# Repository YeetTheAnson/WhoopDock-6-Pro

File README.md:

# WhoopDock 6 Pro

## Introduction

*Up to 130W when powered with VBUS pads

This is my custom BT2.0 battery charger! I started this project because I wanted a programmable 1S LiPo/LiHV multi channel charger that included discharging and storage mode. Commercial chargers like the hexachargers or whoopstor has all the mentioned features but it's limited and lack customizability.

This charger is designed primarily for tinywhoop FPV drone batteries that uses the BetaFPV BT2.0 connector, but its 5A charge current also allows it to be used with larger cylindrical cell batteries for long range drones.

| Feature | WhoopDock 6 Pro | BetaFPV Hexacharger | ViFly WhoopStor V3 |
| --- | --- | --- | --- |
| **Max Charge Current (Per Channel)** | **Up to 5A**  | 3.0A | 1.3A |
| **Max Discharge Current (Per Channel)** | **1.16A** | 0.4A | 0.3A |
| **Custom Discharge Current** | **Yes**  | No | No |
| **Target Voltage Control** | **Fully Customizable** | Presets Only | Presets Only |
| **Voltage Increments** | **16mV** | None (3.85V/4.2V/4.35V) | None (3.8V/3.85V/4.2V/4.35V) |
| **Current Increments** | **64mA** | 500mA | 100mA |
| **Big Colour Screen** | **Yes** | **Yes** | No |
| **Programmability** | **Yes** (Arduino compatible) | No (Closed source) | No (Closed source) |
| **WiFi & Bluetooth** | **Yes** | No | No |
| **Audio Feedback** | **Yes** | **Yes** | **Yes** |
| **Active Cooling** | **Yes** (Programmable fan curve) | **Yes** | **Yes** |
| **Reverse Polarity Protection** | **Yes** | No | **Yes** |

If you don't like how it works, you could always program it to replicate the behavior of your favorite charger.

### Advantages:

* **Current Delivery:** The WhoopDock is much more powerful compared to commercial chargers from BetaFPV and ViFly. With the BQ25890, you can charge large batteries up to 5A, or use the small 64mA interval to precisely control the charge current of small batteries. The 1.16A discharge rate means your large batteries will hit storage voltage way faster, and can be adjusted lower for smaller batteries.
* **Fine Control:** Instead of being forced to choose from specific presets, the 16mV step resolution allows you to charge different battery chemistries or set a custom charge termination voltage.
* **Connectivity:** Having Bluetooth and WiFi onboard allows you to monitor charge cycles from your phone, and receive push notifications when charging is complete.

### Drawbacks:
* **Max power:** While the WhoopDock 60W power is still more than the hexacharger's 24W, the pro version supports up to 78W. The 60W limit is due to the USB C specification, and it supports up to 130W if powered directly by bypassing USB connectors.
* **No PH2.0 connector:** This is intentional by design as PH2.0 is an inferior connector compared to BT2.0, and it only supports a continuous charge current of 2A.

---

## Hardware Specifications

* **MCU:** ESP32-S3-WROOM-1-N8
* **Charge Controller:** 6x TI BQ25890
* **I2C Multiplexer:** TCA9548A
* **PD Negotiation:** CH224K
* **Display:** 1.3" 240x240 ST7789 TFT
* **Power Supply:** XL1509-5.0E1 5V Buck Converter, 2x RT9193 3.3v LDO (One for ESP32 and another to power the display)
* **Active Cooling:** 5V 4010 blower fan and dual 60x20x10mm aluminum heatsinks
* **Protection:** AO4407A P Channel MOSFETs for battery reverse polarity insertion protection

Note: The BQ25890 has a maximum input voltage limit of 14V. The CH224K is configured to negotiate 12V for optimal performance. Do not bridge the 15V or 20V jumpers on the PD controller. Only use 2-3s batteries on the VBUS input pads.

---

> [!WARNING]
> **DO NOT USE THE OCTAL PSRAM VERSION OF THE ESP32S3.** The octal version uses GPIO35, 36 and 37 for memory which overlap with the GPIOs used in the charger. Use QUAD SPI versions otherwise the ESP32 will fail to boot.

## Ports and Interfaces

### External Connections

* **Main Power (Protruding USB C):** This is the primary power input and supports up to 12v 5A (60W)
* **Programming (Flush USB C):** Connected directly to the ESP32 USB data pins for programming. Cannot be accessed while inside the case.
* **Direct Power Pads:** Exposed solder pads on the PCB to bypass the USBC port entirely. Solder XT30 connectors here to bypass the power limit of USB C

### Pinout

| Component | Pin Name | ESP32S3 GPIO | Description |
| --- | --- | --- | --- |
| **TFT Display** | `SCL`| GPIO 35 | SPI Clock |
|  | `TFT_SDA`| GPIO 36 | SPI Data |
|  | `TFT_RES` | GPIO 37 | Display Reset |
|  | `TFT_DC` | GPIO 38 | Data / Command |
|  | `TFT_BLK` | GPIO 39 | Backlight Control |
| **I2C Bus** | `MAIN_SDA` | GPIO 47 | Main I2C Data (TCA9548A MUX) |
|  | `MAIN_SCL` | GPIO 48 | Main I2C Clock (TCA9548A MUX) |
| **User Interface** | `SW_LEFT` | GPIO 8 | Left Button (Active Low) |
|  | `SW_RIGHT` | GPIO 18 | Right Button (Active Low) |
|  | `BUZZER` | GPIO 17 | Passive Buzzer |
| **Cooling** | `FAN` | GPIO 40 | 4010 Fan PWM Power |

*Note: The CE pins are pulled high by 5.1k resistors.*

|Battery Channel | Charge Enable GPIO | Discharge PWM GPIO | TCA9548A MUX Port |
| --- | --- | --- | --- |
| **Channel 1** | GPIO 43 | GPIO 41 | Port 6 |
| **Channel 2** | GPIO 2 | GPIO 42 | Port 5 |
| **Channel 3** | GPIO 1 | GPIO 44 | Port 4 |
| **Channel 4** | GPIO 12 | GPIO 13 | Port 1 |
| **Channel 5** | GPIO 11 | GPIO 14 | Port 2 |
| **Channel 6** | GPIO 10 | GPIO 21 | Port 3 |

---

## Firmware Setup

The current firmware is for connection validation only, and isn't production ready yet. Your batteries WILL charge
### How to flash the firmware

1. **Connect to the Programming Port:** Plug a USBC cable into the flush USBC port (not the protruding power port).
2. **Open Arduino IDE:** Load `firmware/firmware.ino`.
3. **Select Board:** Choose "ESP32S3 Dev Module". Ensure "USB CDC On Boot" is enabled to view the serial monitor for debugging.
4. **Flash:** Click upload. The firmware will initialize the ST7789 display, ramp up and down the fan and buzzer, scans the I2C multiplexer ports and then reports the status of all BQ25890 to the serial monitor.

---

## Case Assembly

### 3D Printed Parts

All STL files for the case is in `/production/3dPrint/`.

* `bottomCase.stl`
* `topCase.stl`
* `Buttons.stl`
* `Feets.stl`

### Assembly

1. Create a solder bridge at CFG3 to set the Ch224K to 12V

2. Trim the BetaFPV BT2.0 connector legs. Make a test fit **before** soldering to ensure it's not protruding.

3. Place the 3D printed `Buttons.stl` into the holes on `topCase.stl`.

4. Screw in the 4010 blower fan into the bottom case using 4x M2x6mm screws.

5. Snap the PCB into the top case.

6. Apply thermal adhesives on the two heatsink and attach to the PCB.

7. Secure the bottom case onto the top case and screw in using 4x M2x6mm screws. Remember to solder the solder the fan wires before closing the case.

8. Attach the TPU  `Feets.stl` to the bottom to cover the screws and prevent sliding. You may use glue to keep the feets in.

---

## Bill of Material

Note: The prices in USD are converted as of 13 August 2026 and prices may fluctuate. Promo codes will be applied before checkout to bring the costs down. And yes, the costs of separate components are cheaper than JLCPCB assembly.

| Item Name | Link | Vendor | Quantity | Total Price (USD) |
| --- | --- | --- | --- | ---: |
| Heatsink 60x20x10mm | [Link](https://shopee.com.my/Heatsink-40x40x11-mm-Aluminium-Clear-Black-Gold-Anodized-i.6674515.812567757) | Shopee | 2 | 0.85 |
| MLT8530 Buzzer 5v | [Link](https://shopee.com.my/5Pcs-SMD-Magnetic-Piezo-Loudspeaker-Speaker-Buzzer-8630-1109-9045-9025-9018-5020-1230-9032-7525-8630-8540-Passive-9650-Active-i.1649836180.27542857025) | Shopee | 1 | 1.45 |
| Capacitor 100nF 50v (0603) | [Link](https://shopee.com.my/100pcs-0603-1608-SMD-Chip-Multilayer-Ceramic-Capacitor-0.1pF-22uF-10pF-22pF-100pF-1nF-10nF-15nF-100nF-0.1uF-1uF-2.2uF-4.7uF-10-i.1649836180.27542857041) | Shopee | 1 | 0.90 |
| Capacitor 10nF 50v (0603) | [Link](https://shopee.com.my/100pcs-0603-1608-SMD-Chip-Multilayer-Ceramic-Capacitor-0.1pF-22uF-10pF-22pF-100pF-1nF-10nF-15nF-100nF-0.1uF-1uF-2.2uF-4.7uF-10-i.1649836180.27542857041) | Shopee | 1 | 0.98 |
| Capacitor 1uF 25v (0603) | [Link](https://shopee.com.my/100pcs-0603-1608-SMD-Chip-Multilayer-Ceramic-Capacitor-0.1pF-22uF-10pF-22pF-100pF-1nF-10nF-15nF-100nF-0.1uF-1uF-2.2uF-4.7uF-10-i.1649836180.27542857041) | Shopee | 1 | 0.91 |
| Capacitor 47nF 50v (0603) | [Link](https://shopee.com.my/100pcs-0603-1608-SMD-Chip-Multilayer-Ceramic-Capacitor-0.1pF-22uF-10pF-22pF-100pF-1nF-10nF-15nF-100nF-0.1uF-1uF-2.2uF-4.7uF-10-i.1649836180.27542857041) | Shopee | 1 | 0.94 |
| Capacitor 4.7uF 16v (0603) | [Link](https://shopee.com.my/100pcs-0603-1608-SMD-Chip-Multilayer-Ceramic-Capacitor-0.1pF-22uF-10pF-22pF-100pF-1nF-10nF-15nF-100nF-0.1uF-1uF-2.2uF-4.7uF-10-i.1649836180.27542857041) | Shopee | 1 | 1.50 |
| Capacitor 10uF 25v (0805) | [Link](https://shopee.com.my/100pcs-0805-SMD-Chip-Multilayer-Ceramic-Capacitor-0.5pF-47uF-10pF-22pF-100pF-1nF-10nF-100nF-0.1uF-1uF-2.2uF-4.7uF-10uF-22uF-i.1649836180.56864018438) | Shopee | 1 | 3.86 |
| Tantalum Capacitor 33uF 10v (A) | [Link](https://shopee.com.my/10Pcs-3216A-SMD-Tantalum-Capacitor-100-220-330-470-1UF-2.2UF-3.3UF-4.7UF-6.8UF-22UF-33UF-47UF-100UF-4V-6.3V-10V-16V-20V-25V-35V-i.1649836180.55607396414) | Shopee | 1 | 1.90 |
| Diode SS14 | [Link](https://shopee.com.my/10-Pieces-SB1045L-SB10100L-SL1045-B240A-SS12-SS14-SS16-SS24-SS26-SS34-SS36-SS54-SS56-SS110-SS210-SS2200-DSK16-DSK24-DSK26-i.1649836180.47204908404) | Shopee | 1 | 0.82 |
| Inductor 1uH (0420) | [Link](https://shopee.com.my/5PCS-SMD-Molding-Power-Inductors-0420-0520-0530-0630-0650-1040-1265-1R0-2R2-6R8-1UH-2.2-3.3-4.7-6.8-33-100UH-2.2UH-Inductance-i.1649836180.45952518693) | Shopee | 2 | 2.10 |
| Resistor 5.1k (0603) | [Link](https://shopee.com.my/200pcs-0603-5-SMD-Resistor-0R-~-10M-1-10W-10-100-150-220-330-470-ohm-1K-2.2K-4.7K-10K-100K-1M-1R-10R-100R-150R-220R-330R-470R-i.1649836180.57850021816) | Shopee | 1 | 0.75 |
| Resistor 10k (0603) | [Link](https://shopee.com.my/200pcs-0603-5-SMD-Resistor-0R-~-10M-1-10W-10-100-150-220-330-470-ohm-1K-2.2K-4.7K-10K-100K-1M-1R-10R-100R-150R-220R-330R-470R-i.1649836180.57850021816) | Shopee | 1 | 0.75 |
| Resistor 1k (0603) | [Link](https://shopee.com.my/200pcs-0603-5-SMD-Resistor-0R-~-10M-1-10W-10-100-150-220-330-470-ohm-1K-2.2K-4.7K-10K-100K-1M-1R-10R-100R-150R-220R-330R-470R-i.1649836180.57850021816) | Shopee | 1 | 0.75 |
| Resistor 100 (0603) | [Link](https://shopee.com.my/200pcs-0603-5-SMD-Resistor-0R-~-10M-1-10W-10-100-150-220-330-470-ohm-1K-2.2K-4.7K-10K-100K-1M-1R-10R-100R-150R-220R-330R-470R-i.1649836180.57850021816) | Shopee | 1 | 0.75 |
| ESP32-S3-WROOM-1-N8 | [Link](https://shopee.com.my/1Pcs-ESP32-S3-ESP32-S3-WROOM-1-1U-ESP32-S3-MINI-1U-4MB-8MB-16MB-N4-N4R2-N4R8-N8-N8R2-N8R8-N16-N16R2-N16R8-WiFi-Ble-5.0-Module-i.1649836180.43173884048) | Shopee | 1 | 6.02 |
| USBC Connector | [Link](https://shopee.com.my/5Pcs-USB-Type-C-3.1-2-6-16-24-Pin-Connector-Female-Jack-Charging-Port-SMD-SMT-PCB-Solder-DIY-Repair-USB-C-Type-C-Socket-i.1649836180.45502078939) | Shopee | 1 | 0.85 |
| Resistor 15 (2512) | [Link](https://shopee.com.my/(20pcs)-2512-SMD-Resistor-0.1R~910R-5-0.2R-0.15R-0.25R-0.22R-0.47R-0R-1R-1.5R-5.1R-2.2R-4.7R-10R-22R-47R-50R-100R-220R-330R-470R-Ohm-Resistance-i.475340513.28383894995) | Shopee | 2 | 1.24 |
| BetaFPV BT2.0 Connector | [Link](https://shopee.com.my/1-Pair-BETAFPV-BT2.0-Connector-BTC2.0-i.92575144.7717088511) | Shopee | 6 | 7.34 |
| N Channel Mosfet AO3400A | [Link](https://shopee.com.my/50pcs-AO3400-SOT23-AO3400A-SOT-23-A09T-SOT-AO3401-AO3402-AO3404-AO3406-AO3407-AO3415-AO3416-SMD-Field-Effect-Management-i.1135937572.24257651124) | Shopee | 1 | 0.85 |
| P Channel Mosfet AO4007A | [Link](https://shopee.com.my/10pcs-lot-AO4407AL-AO4407A-AO4407-4407A-4407-SOP8-30V-12A-P-Channel-MOSFET-In-Stock-i.304553259.7152107243) | Shopee | 1 | 0.92 |
| XL1509-5.0E1 | [Link](https://shopee.com.my/10-PCS-XL1509-ADJE1-XL1509-ADJ-XL1509-5.0E1-XL1509-5.0-XL1509-3.3E1-XL1509-3.3-XL1509-SOP-8-In-Stock-i.304553259.23988849871) | Shopee | 1 | 1.65 |
| BQ25890 | [Link](https://shopee.com.my/5PCS-BQ25601-BQ25890-QFN-BQ25890H-BQ25896-BQ25892RTWR-BQ-series-charging-ics-IC-i.1592750725.44459693293) | Shopee | 2 | 10.00 |
| I2C Multiplexer TCA9548 | [Link](https://shopee.com.my/CJMCU-9548-TCA9548-TCA9548A-1-to-8-I2C-8-way-multi-channel-Expansion-Board-IIC-Module-i.927139050.23724940668) | Shopee | 1 | 0.84 |
| 1.3" TFT Display | [Link](https://shopee.com.my/TFT-Display-0.96-1.3-1.44-Inch-IPS-7P-SPI-HD-65K-Full-Color-LCD-Module-ST7735-Drive-IC-80*160-(Not-OLED)-For-Arduino-i.509537957.11442443894) | Shopee | 1 | 2.72 |
| PCB |  | JLCPCB | 1 | 2.00 |
| SPX Express Shipping |  | Shopee | 9 | 11.45 |
| PCB Shipping |  | JLCPCB | 1 | 1.50 |
| **GRAND TOTAL** |  |  |  | **66.59** |

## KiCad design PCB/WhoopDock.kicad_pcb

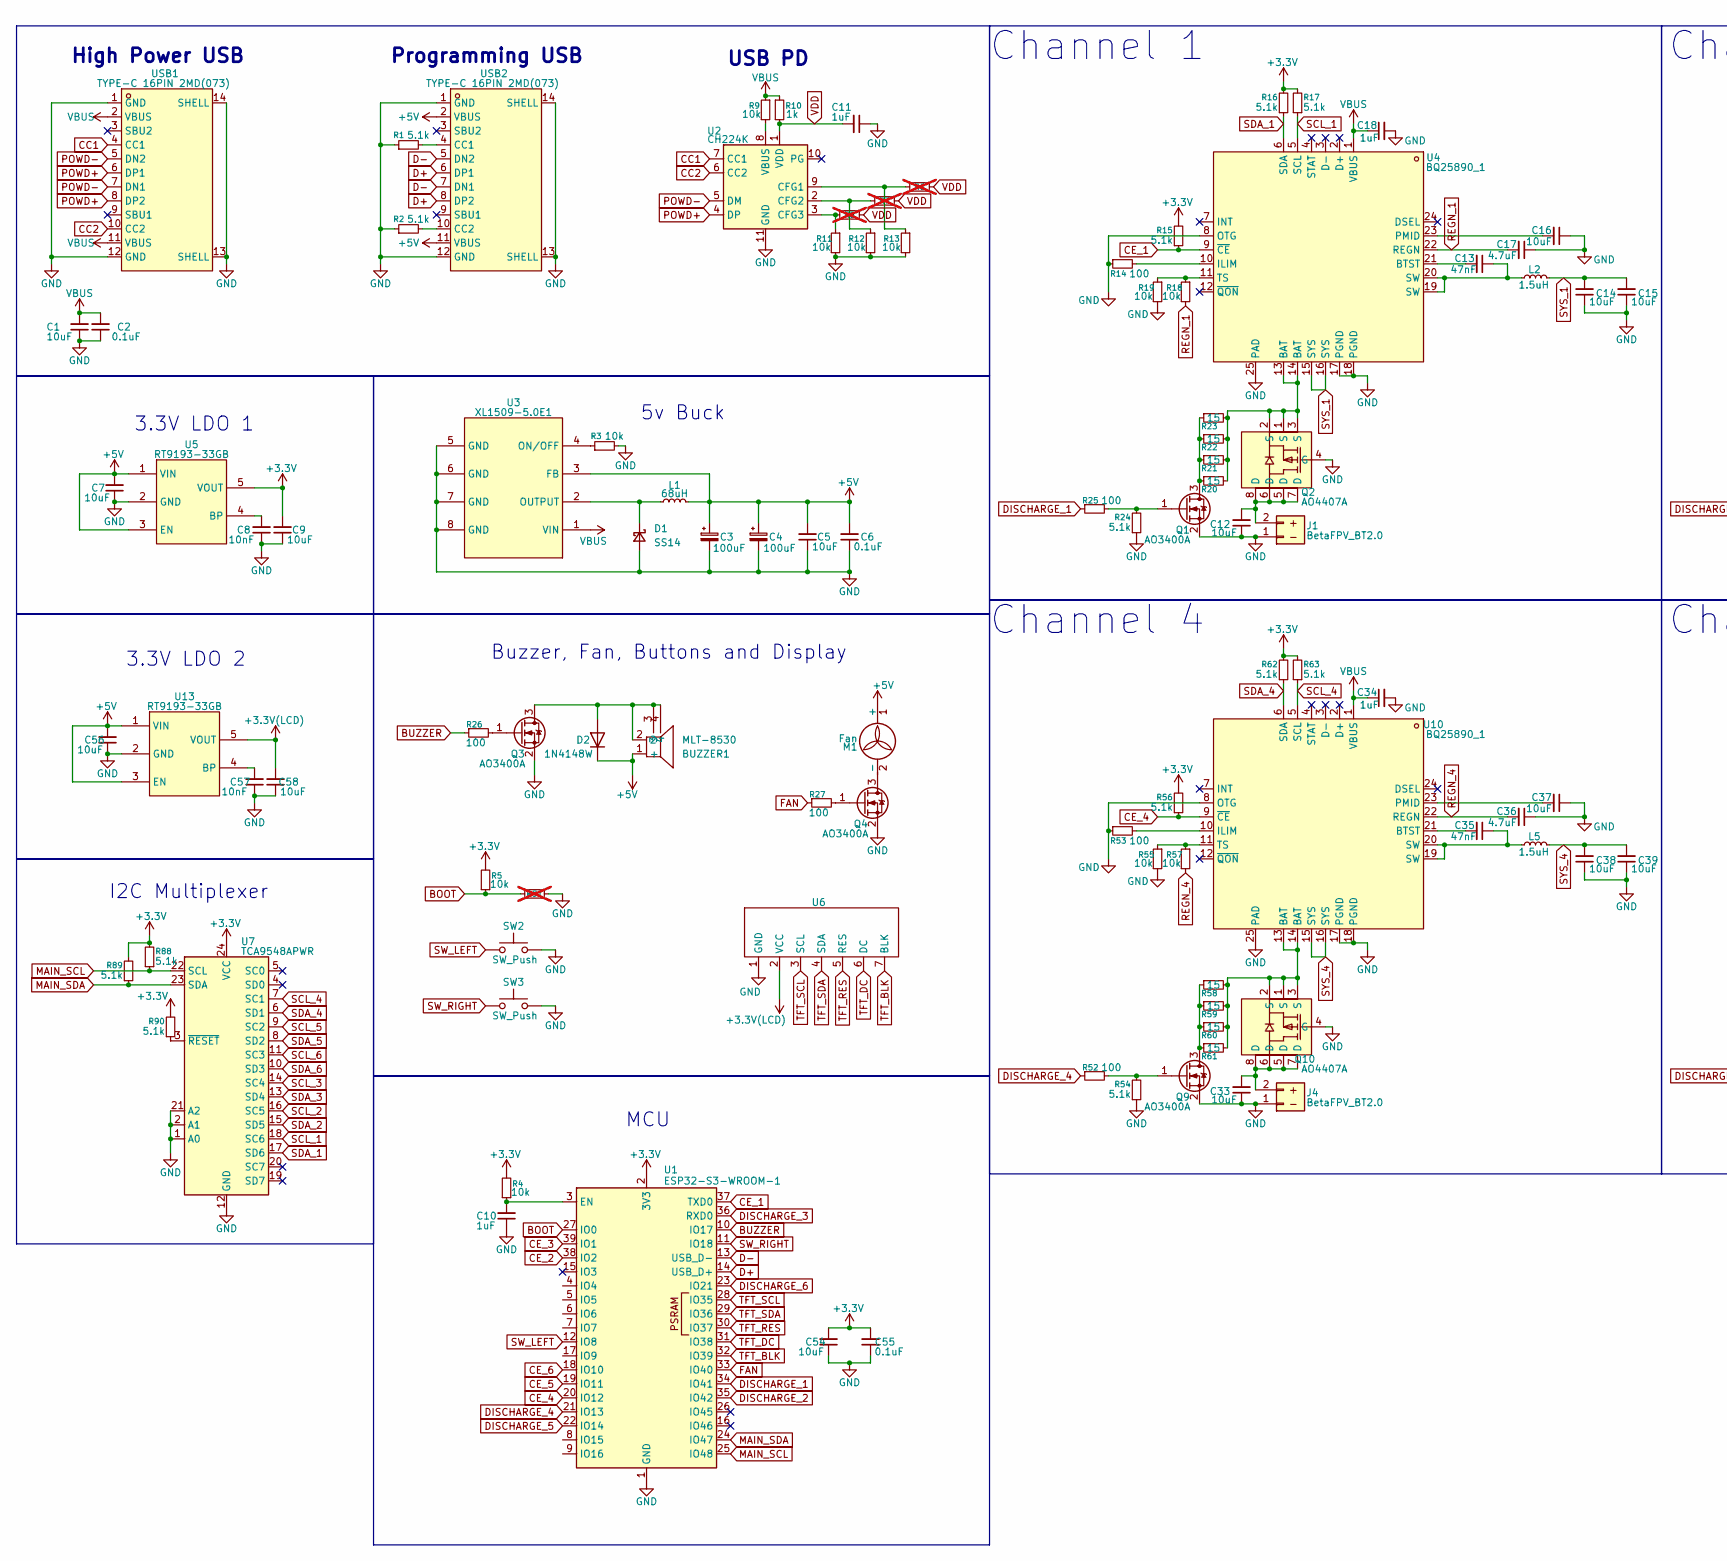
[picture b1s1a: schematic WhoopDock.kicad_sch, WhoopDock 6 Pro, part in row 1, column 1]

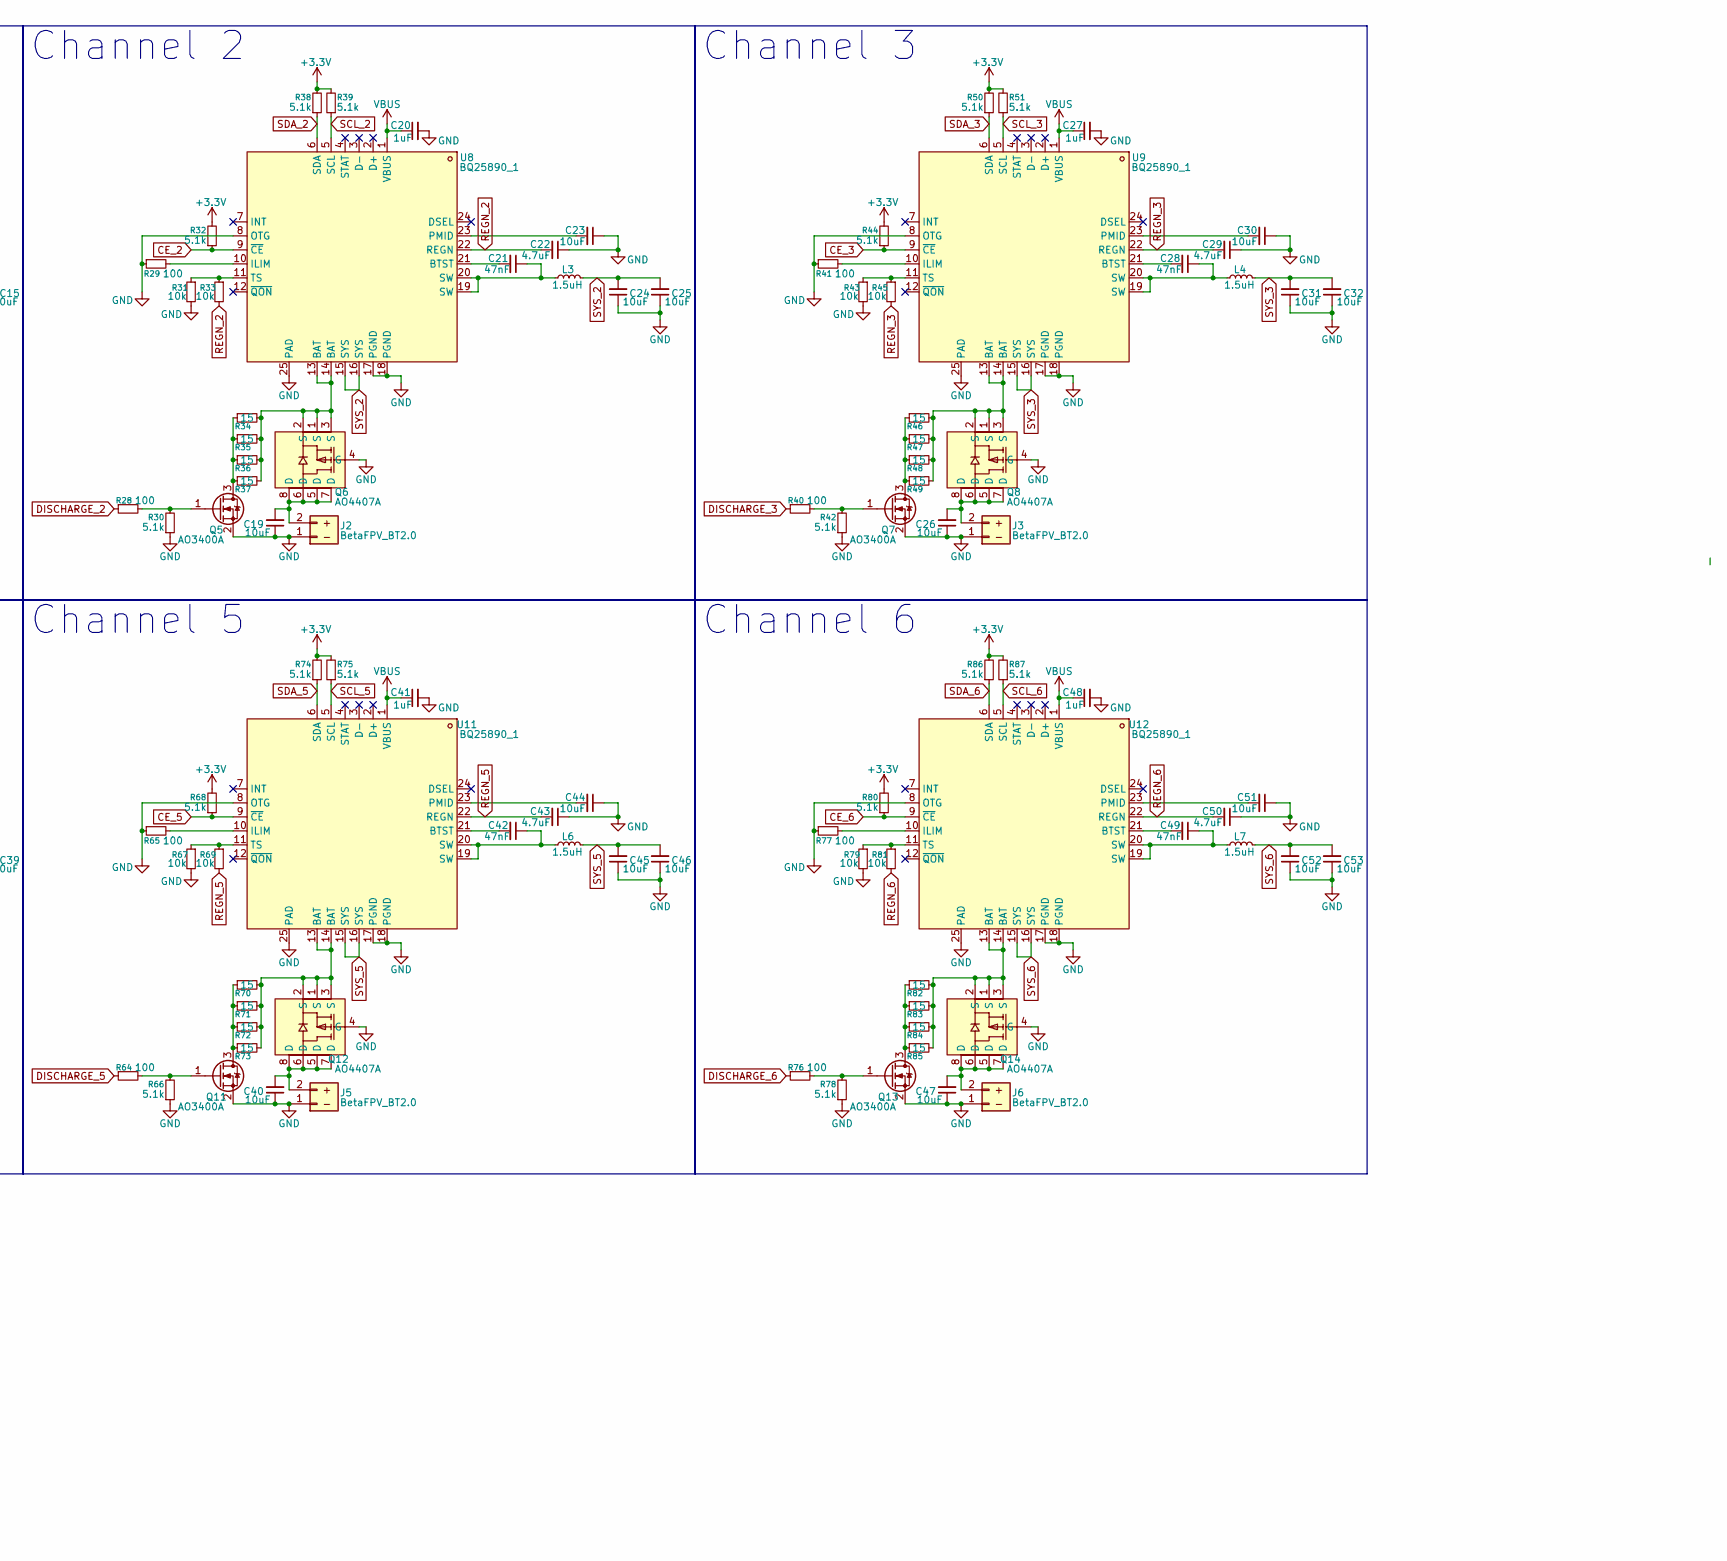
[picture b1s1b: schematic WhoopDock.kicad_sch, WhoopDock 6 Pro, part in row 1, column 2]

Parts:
BUZZER1: MLT-8530; BUZ-SMD_4P-L8.5-W8.5-P8.50-BR; MPN MLT-8530; LCSC Part C94599
C1, C5, C7, C9, C12, C14, C15, C16, C19, C23, C24, C25, C26, C30, C31, C32, C33, C37, C38, C39, C40, C44, C45, C46, C47, C51, C52, C53, C54, C56, C58: 10uF; C_0805_2012Metric; LCSC Part C440198
C2, C6, C55: 0.1uF; C_0603_1608Metric; LCSC Part C14663
C3, C4: 100uF; CP_EIA-3216-18_Kemet-A; LCSC Part C561794
C8, C57: 10nF; C_0603_1608Metric; LCSC Part C57112
C10, C11, C18, C20, C27, C34, C41, C48: 1uF; C_0603_1608Metric; LCSC Part C15849
C13, C21, C28, C35, C42, C49: 47nF; C_0603_1608Metric; LCSC Part C1622
C17, C22, C29, C36, C43, C50: 4.7uF; C_0603_1608Metric; LCSC Part C19666
D1: SS14; D_SMA; LCSC Part C2480
D2: 1N4148W; D_SOD-123F; LCSC Part C108804
J1, J2, J3, J4, J5, J6: BetaFPV_BT2.0; BetaFPV BT2.0
L1: 68uH; L_Sunlord_SWPA8040S; LCSC Part C2894721
L2, L3, L4, L5, L6, L7: 1.5uH; L_APV_APH0420; LCSC Part C167205
M1: Fan
Q1, Q3, Q4, Q5, Q7, Q9, Q11, Q13: AO3400A; SOT-23; LCSC Part C20917
Q2, Q6, Q8, Q10, Q12, Q14: AO4407A; SOIC-8_L4.9-W3.9-P1.27-LS6.0-BL; MPN AO4407A; LCSC Part C16072
R1, R2, R15, R16, R17, R24, R30, R32, R38, R39, R42, R44, R50, R51, R54, R56, R62, R63, R66, R68, R74, R75, R78, R80, R86, R87, R88, R89, R90: 5.1k; R_0603_1608Metric; LCSC Part C23186
R3, R4, R5, R9, R11, R12, R13, R18, R19, R31, R33, R43, R45, R55, R57, R67, R69, R79, R81: 10k; R_0603_1608Metric; LCSC Part C25804
R6, R7, R8, R91: 0; R_0603_1608Metric; not fitted
R10: 1k; R_0603_1608Metric; LCSC Part C21190
R14, R25, R26, R27, R28, R29, R40, R41, R52, R53, R64, R65, R76, R77: 100; R_0603_1608Metric; LCSC Part C22775
R20, R21, R22, R23, R34, R35, R36, R37, R46, R47, R48, R49, R58, R59, R60, R61, R70, R71, R72, R73, R82, R83, R84, R85: 15; R_2512_6332Metric; LCSC Part C20087
SW2, SW3: SW_Push; SW_PUSH_6mm_H5mm; LCSC Part C2837531
U1: ESP32-S3-WROOM-1; LCSC Part C2913198
U2: CH224K; SSOP-10-1EP_3.9x4.9mm_P1mm_EP2.1x3.3mm; LCSC Part C970725
U3: XL1509-5.0E1; SOIC-8_L5.0-W4.0-P1.27-LS6.0-BL; MPN XL1509-5.0E1; LCSC Part C61063
U4, U8, U9, U10, U11, U12: BQ25890_1; WQFN-24_L4.0-W4.0-P0.50-BL-EP; MPN BQ25890RTWR; LCSC Part C130451
U5, U13: RT9193-33GB; SOT-23-5_L3.0-W1.7-P0.95-LS2.8-BL; MPN RT9193-33GB; LCSC Part C15651
U6: 1.3 TFT
U7: TCA9548APWR; TSSOP-24_4.4x7.8mm_P0.65mm; LCSC Part C130026
USB1, USB2: TYPE-C 16PIN 2MD(073); USB-C-SMD_TYPE-C-6PIN-2MD-073; LCSC Part C2765186

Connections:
+3.3V: C9.2, C54.2, C55.2, R4.2, R5.2, R15.2, R16.2, R17.2, R32.2, R38.2, R39.2, R44.2, R50.2, R51.2, R56.2, R62.2, R63.2, R68.2, R74.2, R75.2, R80.2, R86.2, R87.2, R88.2, R89.2, R90.2, U1.2 (3V3), U5.5 (VOUT), U7.24 (VCC)
+3.3V(LCD): C58.2, U6.2 (VCC), U13.5 (VOUT)
+5V: BUZZER1.1 (+), C3.1, C4.1, C5.2, C6.2, C7.2, C56.2, D2.1 (K), L1.2, M1.1 (+), U3.3 (FB), U5.1 (VIN), U5.3 (EN), U13.1 (VIN), U13.3 (EN), USB2.2 (VBUS), USB2.11 (VBUS)
BOOT: R5.1, R91.1, U1.27 (IO0)
BUZZER: R26.1, U1.10 (IO17)
CC1: U2.7 (CC1), USB1.4 (CC1)
CC2: U2.6 (CC2), USB1.10 (CC2)
CE_1: R15.1, U1.37 (TXD0), U4.9 (~CE)
CE_2: R32.1, U1.38 (IO2), U8.9 (~CE)
CE_3: R44.1, U1.39 (IO1), U9.9 (~CE)
CE_4: R56.1, U1.20 (IO12), U10.9 (~CE)
CE_5: R68.1, U1.19 (IO11), U11.9 (~CE)
CE_6: R80.1, U1.18 (IO10), U12.9 (~CE)
D+: U1.14 (USB_D+), USB2.6 (DP1), USB2.8 (DP2)
D-: U1.13 (USB_D-), USB2.5 (DN2), USB2.7 (DN1)
DISCHARGE_1: R25.1, U1.34 (IO41)
DISCHARGE_2: R28.1, U1.35 (IO42)
DISCHARGE_3: R40.1, U1.36 (RXD0)
DISCHARGE_4: R52.1, U1.21 (IO13)
DISCHARGE_5: R64.1, U1.22 (IO14)
DISCHARGE_6: R76.1, U1.23 (IO21)
FAN: R27.1, U1.33 (IO40)
GND: C1.1, C2.1, C3.2, C4.2, C5.1, C6.1, C7.1, C8.1, C9.1, C10.1, C11.1, C12.1, C14.1, C15.1, C16.1, C17.1, C18.2, C19.1, C20.2, C22.1, C23.1, C24.1, C25.1, C26.1, C27.2, C29.1, C30.1, C31.1, C32.1, C33.1, C34.2, C36.1, C37.1, C38.1, C39.1, C40.1, C41.2, C43.1, C44.1, C45.1, C46.1, C47.1, C48.2, C50.1, C51.1, C52.1, C53.1, C54.1, C55.1, C56.1, C57.1, C58.1, D1.2 (A), J1.1, J2.1, J3.1, J4.1, J5.1, J6.1, Q1.2 (S), Q2.4 (G), Q3.2 (S), Q4.2 (S), Q5.2 (S), Q6.4 (G), Q7.2 (S), Q8.4 (G), Q9.2 (S), Q10.4 (G), Q11.2 (S), Q12.4 (G), Q13.2 (S), Q14.4 (G), R1.1, R2.1, R3.2, R11.2, R12.2, R13.2, R14.1, R19.2, R24.1, R29.1, R30.1, R31.2, R41.1, R42.1, R43.2, R53.1, R54.1, R55.2, R65.1, R66.1, R67.2, R77.1, R78.1, R79.2, R91.2, SW2.2, SW3.2, U1.1 (GND), U1.40 (GND), U1.41 (GND), U2.11 (GND), U3.5 (GND), U3.6 (GND), U3.7 (GND), U3.8 (GND), U4.8 (OTG), U4.17 (PGND), U4.18 (PGND), U4.25 (PAD), U5.2 (GND), U6.1 (GND), U7.1 (A0), U7.2 (A1), U7.12 (GND), U7.21 (A2), U8.8 (OTG), U8.17 (PGND), U8.18 (PGND), U8.25 (PAD), U9.8 (OTG), U9.17 (PGND), U9.18 (PGND), U9.25 (PAD), U10.8 (OTG), U10.17 (PGND), U10.18 (PGND), U10.25 (PAD), U11.8 (OTG), U11.17 (PGND), U11.18 (PGND), U11.25 (PAD), U12.8 (OTG), U12.17 (PGND), U12.18 (PGND), U12.25 (PAD), U13.2 (GND), USB1.1 (GND), USB1.12 (GND), USB1.13 (SHELL), USB1.14 (SHELL), USB2.1 (GND), USB2.12 (GND), USB2.13 (SHELL), USB2.14 (SHELL)
MAIN_SCL: R88.1, U1.25 (IO48), U7.22 (SCL)
MAIN_SDA: R89.1, U1.24 (IO47), U7.23 (SDA)
unnamed: C13.1, L2.1, U4.19 (SW), U4.20 (SW)
unnamed: C21.1, L3.1, U8.19 (SW), U8.20 (SW)
unnamed: C28.1, L4.1, U9.19 (SW), U9.20 (SW)
unnamed: C35.1, L5.1, U10.19 (SW), U10.20 (SW)
unnamed: C42.1, L6.1, U11.19 (SW), U11.20 (SW)
unnamed: C49.1, L7.1, U12.19 (SW), U12.20 (SW)
unnamed: D1.1 (K), L1.1, U3.2 (OUTPUT)
unnamed: BUZZER1.2, BUZZER1.3, BUZZER1.4, D2.2 (A), Q3.3 (D)
unnamed: C12.2, J1.2, Q2.5 (D), Q2.6 (D), Q2.7 (D), Q2.8 (D)
unnamed: C19.2, J2.2, Q6.5 (D), Q6.6 (D), Q6.7 (D), Q6.8 (D)
unnamed: C26.2, J3.2, Q8.5 (D), Q8.6 (D), Q8.7 (D), Q8.8 (D)
unnamed: C33.2, J4.2, Q10.5 (D), Q10.6 (D), Q10.7 (D), Q10.8 (D)
unnamed: C40.2, J5.2, Q12.5 (D), Q12.6 (D), Q12.7 (D), Q12.8 (D)
unnamed: C47.2, J6.2, Q14.5 (D), Q14.6 (D), Q14.7 (D), Q14.8 (D)
unnamed: M1.2 (-), Q4.3 (D)
unnamed: Q1.3 (D), R20.1, R21.1, R22.1, R23.1
unnamed: Q1.1 (G), R24.2, R25.2
unnamed: Q2.1 (S), Q2.2 (S), Q2.3 (S), R20.2, R21.2, R22.2, R23.2, U4.13 (BAT), U4.14 (BAT)
unnamed: Q3.1 (G), R26.2
unnamed: Q4.1 (G), R27.2
unnamed: Q5.3 (D), R34.1, R35.1, R36.1, R37.1
unnamed: Q5.1 (G), R28.2, R30.2
unnamed: Q6.1 (S), Q6.2 (S), Q6.3 (S), R34.2, R35.2, R36.2, R37.2, U8.13 (BAT), U8.14 (BAT)
unnamed: Q7.3 (D), R46.1, R47.1, R48.1, R49.1
unnamed: Q7.1 (G), R40.2, R42.2
unnamed: Q8.1 (S), Q8.2 (S), Q8.3 (S), R46.2, R47.2, R48.2, R49.2, U9.13 (BAT), U9.14 (BAT)
unnamed: Q9.3 (D), R58.1, R59.1, R60.1, R61.1
unnamed: Q9.1 (G), R52.2, R54.2
unnamed: Q10.1 (S), Q10.2 (S), Q10.3 (S), R58.2, R59.2, R60.2, R61.2, U10.13 (BAT), U10.14 (BAT)
unnamed: Q11.3 (D), R70.1, R71.1, R72.1, R73.1
unnamed: Q11.1 (G), R64.2, R66.2
unnamed: Q12.1 (S), Q12.2 (S), Q12.3 (S), R70.2, R71.2, R72.2, R73.2, U11.13 (BAT), U11.14 (BAT)
unnamed: Q13.3 (D), R82.1, R83.1, R84.1, R85.1
unnamed: Q13.1 (G), R76.2, R78.2
unnamed: Q14.1 (S), Q14.2 (S), Q14.3 (S), R82.2, R83.2, R84.2, R85.2, U12.13 (BAT), U12.14 (BAT)
unnamed: C10.2, R4.1, U1.3 (EN)
unnamed: R6.1, R13.1, U2.9 (CFG1)
unnamed: R7.1, R12.1, U2.2 (CFG2)
unnamed: R8.1, R11.1, U2.3 (CFG3)
unnamed: R9.2, U2.8 (VBUS)
unnamed: R3.1, U3.4 (ON/OFF)
unnamed: C13.2, U4.21 (BTST)
unnamed: R14.2, U4.10 (ILIM)
unnamed: C16.2, U4.23 (PMID)
unnamed: R18.1, R19.1, U4.11 (TS)
unnamed: C8.2, U5.4 (BP)
unnamed: R90.1, U7.3 (~RESET)
unnamed: C21.2, U8.21 (BTST)
unnamed: R29.2, U8.10 (ILIM)
unnamed: C23.2, U8.23 (PMID)
unnamed: R31.1, R33.1, U8.11 (TS)
unnamed: C28.2, U9.21 (BTST)
unnamed: R41.2, U9.10 (ILIM)
unnamed: C30.2, U9.23 (PMID)
unnamed: R43.1, R45.1, U9.11 (TS)
unnamed: C35.2, U10.21 (BTST)
unnamed: R53.2, U10.10 (ILIM)
unnamed: C37.2, U10.23 (PMID)
unnamed: R55.1, R57.1, U10.11 (TS)
unnamed: C42.2, U11.21 (BTST)
unnamed: R65.2, U11.10 (ILIM)
unnamed: C44.2, U11.23 (PMID)
unnamed: R67.1, R69.1, U11.11 (TS)
unnamed: C49.2, U12.21 (BTST)
unnamed: R77.2, U12.10 (ILIM)
unnamed: C51.2, U12.23 (PMID)
unnamed: R79.1, R81.1, U12.11 (TS)
unnamed: C57.2, U13.4 (BP)
unnamed: R1.2, USB2.4 (CC1)
unnamed: R2.2, USB2.10 (CC2)
POWD+: U2.4 (DP), USB1.6 (DP1), USB1.8 (DP2)
POWD-: U2.5 (DM), USB1.5 (DN2), USB1.7 (DN1)
REGN_1: C17.2, R18.2, U4.22 (REGN)
REGN_2: C22.2, R33.2, U8.22 (REGN)
REGN_3: C29.2, R45.2, U9.22 (REGN)
REGN_4: C36.2, R57.2, U10.22 (REGN)
REGN_5: C43.2, R69.2, U11.22 (REGN)
REGN_6: C50.2, R81.2, U12.22 (REGN)
SCL_1: R17.1, U4.5 (SCL), U7.18 (SC6)
SCL_2: R39.1, U7.16 (SC5), U8.5 (SCL)
SCL_3: R51.1, U7.14 (SC4), U9.5 (SCL)
SCL_4: R63.1, U7.7 (SC1), U10.5 (SCL)
SCL_5: R75.1, U7.9 (SC2), U11.5 (SCL)
SCL_6: R87.1, U7.11 (SC3), U12.5 (SCL)
SDA_1: R16.1, U4.6 (SDA), U7.17 (SD6)
SDA_2: R38.1, U7.15 (SD5), U8.6 (SDA)
SDA_3: R50.1, U7.13 (SD4), U9.6 (SDA)
SDA_4: R62.1, U7.6 (SD1), U10.6 (SDA)
SDA_5: R74.1, U7.8 (SD2), U11.6 (SDA)
SDA_6: R86.1, U7.10 (SD3), U12.6 (SDA)
SW_LEFT: SW2.1, U1.12 (IO8)
SW_RIGHT: SW3.1, U1.11 (IO18)
SYS_1: C14.2, C15.2, L2.2, U4.15 (SYS), U4.16 (SYS)
SYS_2: C24.2, C25.2, L3.2, U8.15 (SYS), U8.16 (SYS)
SYS_3: C31.2, C32.2, L4.2, U9.15 (SYS), U9.16 (SYS)
SYS_4: C38.2, C39.2, L5.2, U10.15 (SYS), U10.16 (SYS)
SYS_5: C45.2, C46.2, L6.2, U11.15 (SYS), U11.16 (SYS)
SYS_6: C52.2, C53.2, L7.2, U12.15 (SYS), U12.16 (SYS)
TFT_BLK: U1.32 (IO39), U6.7 (BLK)
TFT_DC: U1.31 (IO38), U6.6 (DC)
TFT_RES: U1.30 (IO37), U6.5 (RES)
TFT_SCL: U1.28 (IO35), U6.3 (SCL)
TFT_SDA: U1.29 (IO36), U6.4 (SDA)
VBUS: C1.2, C2.2, C18.1, C20.1, C27.1, C34.1, C41.1, C48.1, R9.1, R10.1, U3.1 (VIN), U4.1 (VBUS), U8.1 (VBUS), U9.1 (VBUS), U10.1 (VBUS), U11.1 (VBUS), U12.1 (VBUS), USB1.2 (VBUS), USB1.11 (VBUS)
VDD: C11.2, R6.2, R7.2, R8.2, R10.2, U2.1 (VDD)

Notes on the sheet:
High Power USB
3.3V LDO 1
USB PD
Channel 1
5v Buck
Buzzer, Fan, Buttons and Display
Channel 3
3.3V LDO 2
I2C Multiplexer
Channel 5
Channel 6
Channel 2
Programming USB
Channel 4
MCU

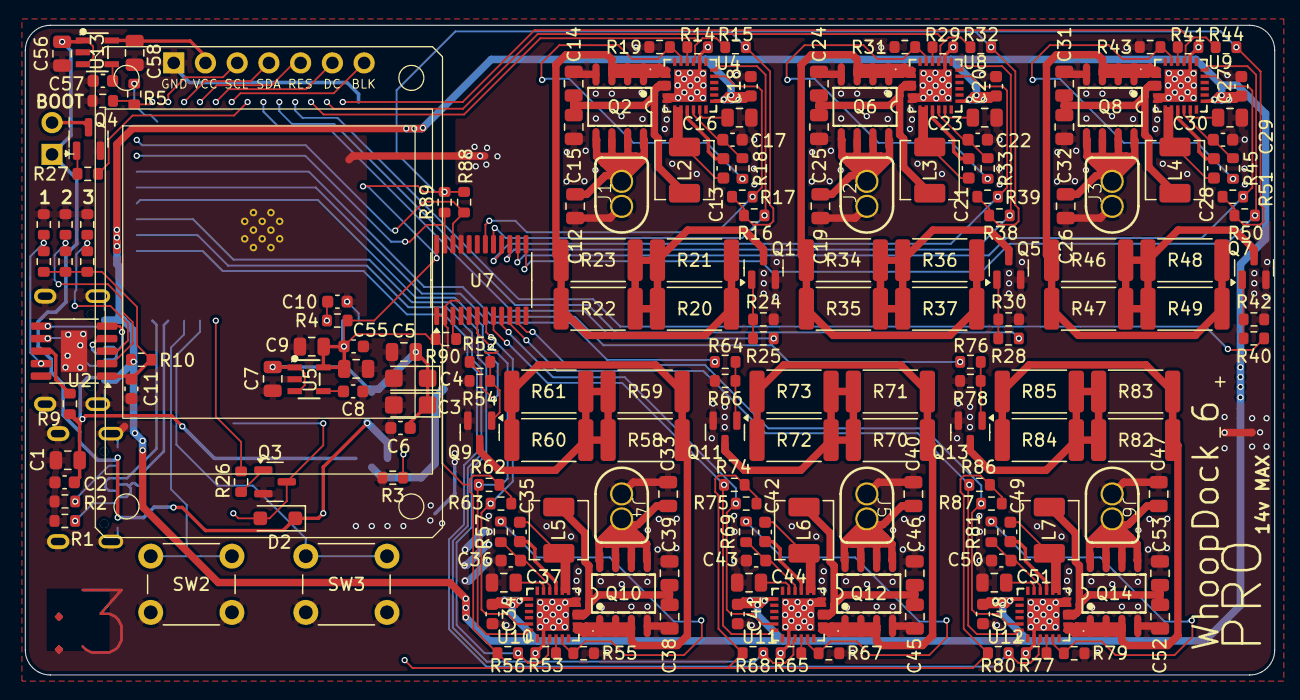
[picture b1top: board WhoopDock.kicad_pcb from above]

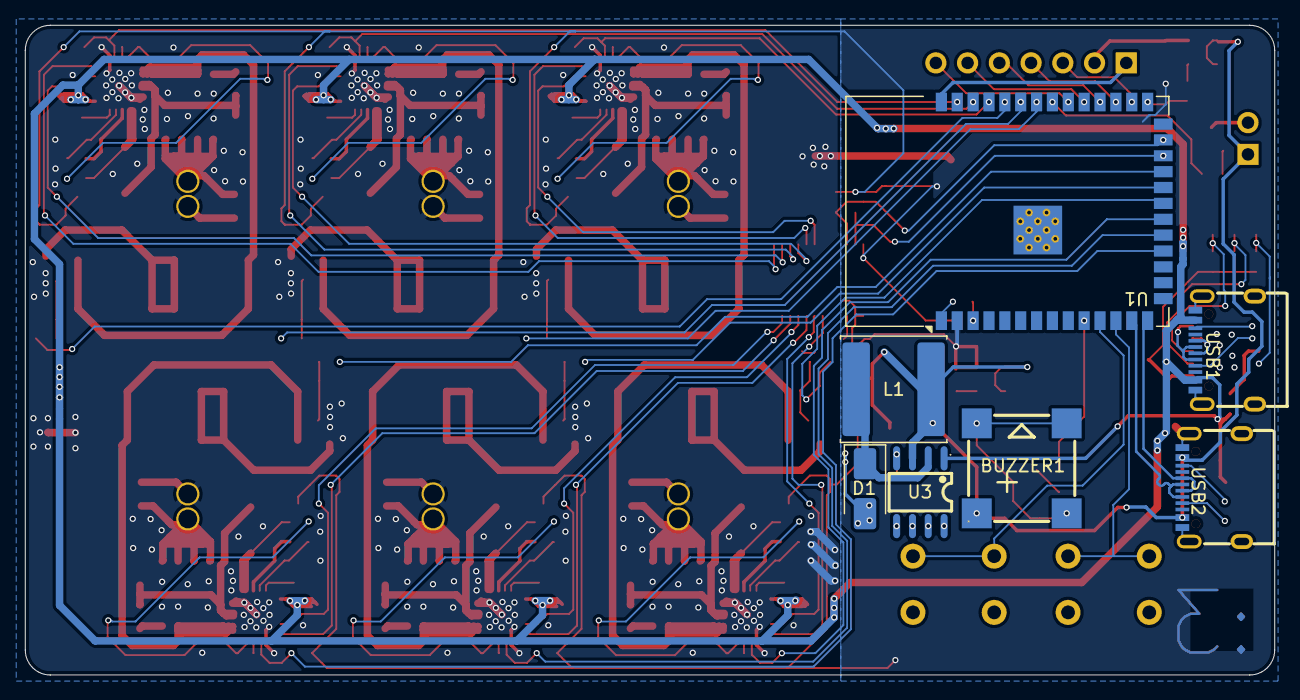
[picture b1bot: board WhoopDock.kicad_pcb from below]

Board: 2 copper layers, 100.0 x 52.0 mm, 197 parts (7 on the bottom side), 130 nets.

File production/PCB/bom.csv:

Designator,Footprint,Quantity,Value,LCSC Part #
BUZZER1,BUZ-SMD_4P-L8.5-W8.5-P8.50-BR,1,MLT-8530,C94599
"C1, C12, C14, C15, C16, C19, C23, C24, C25, C26, C30, C31, C32, C33, C37, C38, C39, C40, C44, C45, C46, C47, C5, C51, C52, C53, C54, C56, C58, C7, C9",0805,31,10uF,C440198
"C10, C11, C18, C20, C27, C34, C41, C48",0603,8,1uF,C15849
"C13, C21, C28, C35, C42, C49",0603,6,47nF,C1622
"C17, C22, C29, C36, C43, C50",0603,6,4.7uF,C19666
"C2, C55, C6",0603,3,0.1uF,C14663
"C3, C4",CP_EIA-3216-18_Kemet-A,2,100uF,C561794
"C57, C8",0603,2,10nF,C57112
D1,D_SMA,1,SS14,C2480
D2,D_SOD-123F,1,1N4148W,C108804
"J1, J2, J3, J4, J5, J6",BetaFPV BT2.0,6,BetaFPV_BT2.0,
L1,L_Sunlord_SWPA8040S,1,68uH,C2894721
"L2, L3, L4, L5, L6, L7",L_APV_APH0420,6,1.5uH,C167205
M1,Fan,1,Fan,
"Q1, Q11, Q13, Q3, Q4, Q5, Q7, Q9",SOT-23,8,AO3400A,C20917
"Q10, Q12, Q14, Q2, Q6, Q8",SOIC-8_L4.9-W3.9-P1.27-LS6.0-BL,6,AO4407A,C16072
"R1, R15, R16, R17, R2, R24, R30, R32, R38, R39, R42, R44, R50, R51, R54, R56, R62, R63, R66, R68, R74, R75, R78, R80, R86, R87, R88, R89, R90",0603,29,5.1k,C23186
R10,0603,1,1k,C21190
"R11, R12, R13, R18, R19, R3, R31, R33, R4, R43, R45, R5, R55, R57, R67, R69, R79, R81, R9",0603,19,10k,C25804
"R14, R25, R26, R27, R28, R29, R40, R41, R52, R53, R64, R65, R76, R77",0603,14,100,C22775
"R20, R21, R22, R23, R34, R35, R36, R37, R46, R47, R48, R49, R58, R59, R60, R61, R70, R71, R72, R73, R82, R83, R84, R85",2512,24,15,C20087
"R6, R7, R8, R91",0603,4,0,
"SW2, SW3",SW_PUSH_6mm_H5mm,2,SW_Push,C2837531
U1,ESP32-S3-WROOM-1,1,ESP32-S3-WROOM-1,C2913198
"U10, U11, U12, U4, U8, U9",WQFN-24_L4.0-W4.0-P0.50-BL-EP,6,BQ25890_1,C130451
"U13, U5",SOT-23-5_L3.0-W1.7-P0.95-LS2.8-BL,2,RT9193-33GB,C15651
U2,SSOP-10-1EP_3.9x4.9mm_P1mm_EP2.1x3.3mm,1,CH224K,C970725
U3,SOIC-8_L5.0-W4.0-P1.27-LS6.0-BL,1,XL1509-5.0E1,C61063
U6,1.3 TFT,1,~,
U7,TSSOP-24_4.4x7.8mm_P0.65mm,1,TCA9548APWR,C130026
"USB1, USB2",USB-C-SMD_TYPE-C-6PIN-2MD-073,2,TYPE-C 16PIN 2MD(073),C2765186

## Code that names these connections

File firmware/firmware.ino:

// Generated by Gemini
#include <Wire.h>
#include <SPI.h>
#include <Adafruit_GFX.h>
#include <Adafruit_ST7789.h>

// ==========================================
// PIN DEFINITIONS
// ==========================================

// --- TFT Screen (1.3" 240x240 ST7789) ---
// Note: CS pin is assumed grounded/absent on this module
#define TFT_SCL 35 // SPI SCK
#define TFT_SDA 36 // SPI MOSI
#define TFT_RES 37 // Reset
#define TFT_DC  38 // Data/Command
#define TFT_BLK 39 // Backlight

// --- I2C & Multiplexer ---
#define I2C_SDA 47
#define I2C_SCL 48
#define TCA_ADDR 0x70
#define BQ25890_ADDR 0x6A // Default I2C address for BQ25890

// --- Fan & Buzzer (PWM) ---
#define FAN_PIN 40
#define BUZZER_PIN 17

// --- Buttons ---
#define BTN_LEFT 8
#define BTN_RIGHT 18

// --- Channel Arrays (1 to 6) ---
// ESP32-S3 Defaults: RXD0 is GPIO44, TXD0 is GPIO43
const uint8_t DISCHARGE_PINS[6] = {41, 42, 44, 13, 14, 21};
const uint8_t CE_PINS[6]        = {43, 2, 1, 12, 11, 10};

// TCA9548A Ports mapped to Channels 1-6: S6, S5, S4, S1, S2, S3
const uint8_t TCA_PORTS[6]      = {6, 5, 4, 1, 2, 3};

// Initialize TFT Display (-1 for CS since it is unused/grounded)
Adafruit_ST7789 tft = Adafruit_ST7789(-1, TFT_DC, TFT_SDA, TFT_SCL, TFT_RES);

// ==========================================
// HELPER FUNCTIONS
// ==========================================

// Switch the TCA9548A multiplexer to a specific port
void tcaSelectPort(uint8_t port) {
  if (port > 7) return;
  Wire.beginTransmission(TCA_ADDR);
  Wire.write(1 << port); 
  Wire.endTransmission();
}

// Example function: Read the system status register from BQ25890
uint8_t readBQ25890Status(uint8_t channelIndex) {
  // 1. Switch I2C Mux to the correct port for this channel
  tcaSelectPort(TCA_PORTS[channelIndex]);
  
  // 2. Request Register 0x0B (System Status Register)
  Wire.beginTransmission(BQ25890_ADDR);
  Wire.write(0x0B); 
  Wire.endTransmission(false); // Repeated start
  
  Wire.requestFrom(BQ25890_ADDR, 1);
  if (Wire.available()) {
    return Wire.read();
  }
  return 0xFF; // Return error state if nothing read
}

// ==========================================
// MAIN SETUP
// ==========================================

void setup() {
  Serial.begin(115200);
  delay(1000); // Give Serial time to initialize
  
  Serial.println("Starting Charge Controller...");

  // 1. Initialize I2C Bus (with external pullups on the multiplexer)
  Wire.begin(I2C_SDA, I2C_SCL);
  Wire.setClock(400000); // Fast I2C

  // 2. Initialize Buttons (Internal Pullups)
  pinMode(BTN_LEFT, INPUT_PULLUP);
  pinMode(BTN_RIGHT, INPUT_PULLUP);

  // 3. Initialize Fan and Buzzer
  pinMode(FAN_PIN, OUTPUT);
  pinMode(BUZZER_PIN, OUTPUT);
  analogWrite(FAN_PIN, 0);    // Turn off fan initially
  analogWrite(BUZZER_PIN, 0); // Turn off buzzer initially

  // 4. Initialize Channel Pins
  for (int i = 0; i < 6; i++) {
    // Dischargers
    pinMode(DISCHARGE_PINS[i], OUTPUT);
    analogWrite(DISCHARGE_PINS[i], 0); // 0% duty cycle (Off)

    // BQ25890 Charge Enable (CE)
    // Note: BQ25890 CE pin is usually Active LOW. High = Disabled, Low = Enabled.
    pinMode(CE_PINS[i], OUTPUT);
    digitalWrite(CE_PINS[i], HIGH); // Default to disabled for safety
  }

  // 5. Initialize TFT Display
  pinMode(TFT_BLK, OUTPUT);
  digitalWrite(TFT_BLK, HIGH); // Turn on backlight
  
  tft.init(240, 240); // Initialize standard 240x240 TFT
  tft.setRotation(2); // Adjust 0-3 depending on your screen orientation
  tft.fillScreen(ST77XX_BLACK);
  
  // Draw Initial UI
  tft.setCursor(10, 10);
  tft.setTextColor(ST77XX_WHITE);
  tft.setTextSize(2);
  tft.println("Controller Init");
  tft.println("Status: OK");
}

// ==========================================
// MAIN LOOP
// ==========================================

void loop() {
  // 1. Handle Button Inputs
  if (digitalRead(BTN_LEFT) == LOW) {
    Serial.println("Left Button Pressed");
    // Add debounce & logic here
    delay(200); 
  }
  
  if (digitalRead(BTN_RIGHT) == LOW) {
    Serial.println("Right Button Pressed");
    // Add debounce & logic here
    delay(200); 
  }

  // 2. Scan BQ25890 Statuses via Multiplexer
  // (We'll print them to Serial, but you can draw them to the TFT later)
  for (int i = 0; i < 6; i++) {
    uint8_t status = readBQ25890Status(i);
    
    // Check if communication failed
    if(status == 0xFF) {
      Serial.printf("Ch %d (Mux Port %d): BQ25890 Not Found\n", i+1, TCA_PORTS[i]);
    } else {
      // VBUS Status is bits 7:6 in reg 0x0B
      uint8_t vbusStat = (status & 0b11000000) >> 6;
      Serial.printf("Ch %d (Mux Port %d): Status Reg 0x%02X | VBUS: %d\n", i+1, TCA_PORTS[i], status, vbusStat);
    }
  }
  
  Serial.println("-------------------------");
  
  // 3. Example: Update Display dynamically
  tft.fillRect(10, 50, 220, 40, ST77XX_BLACK); // Clear previous text area
  tft.setCursor(10, 50);
  tft.setTextColor(ST77XX_GREEN);
  tft.setTextSize(2);
  tft.printf("Uptime: %lu s", millis() / 1000);

  // 4. Example: Fan Control (Sweep 0 to 255)
  // analogWrite(FAN_PIN, 128); // 50% Speed

  delay(1000); // Wait 1 second before next cycle
}
